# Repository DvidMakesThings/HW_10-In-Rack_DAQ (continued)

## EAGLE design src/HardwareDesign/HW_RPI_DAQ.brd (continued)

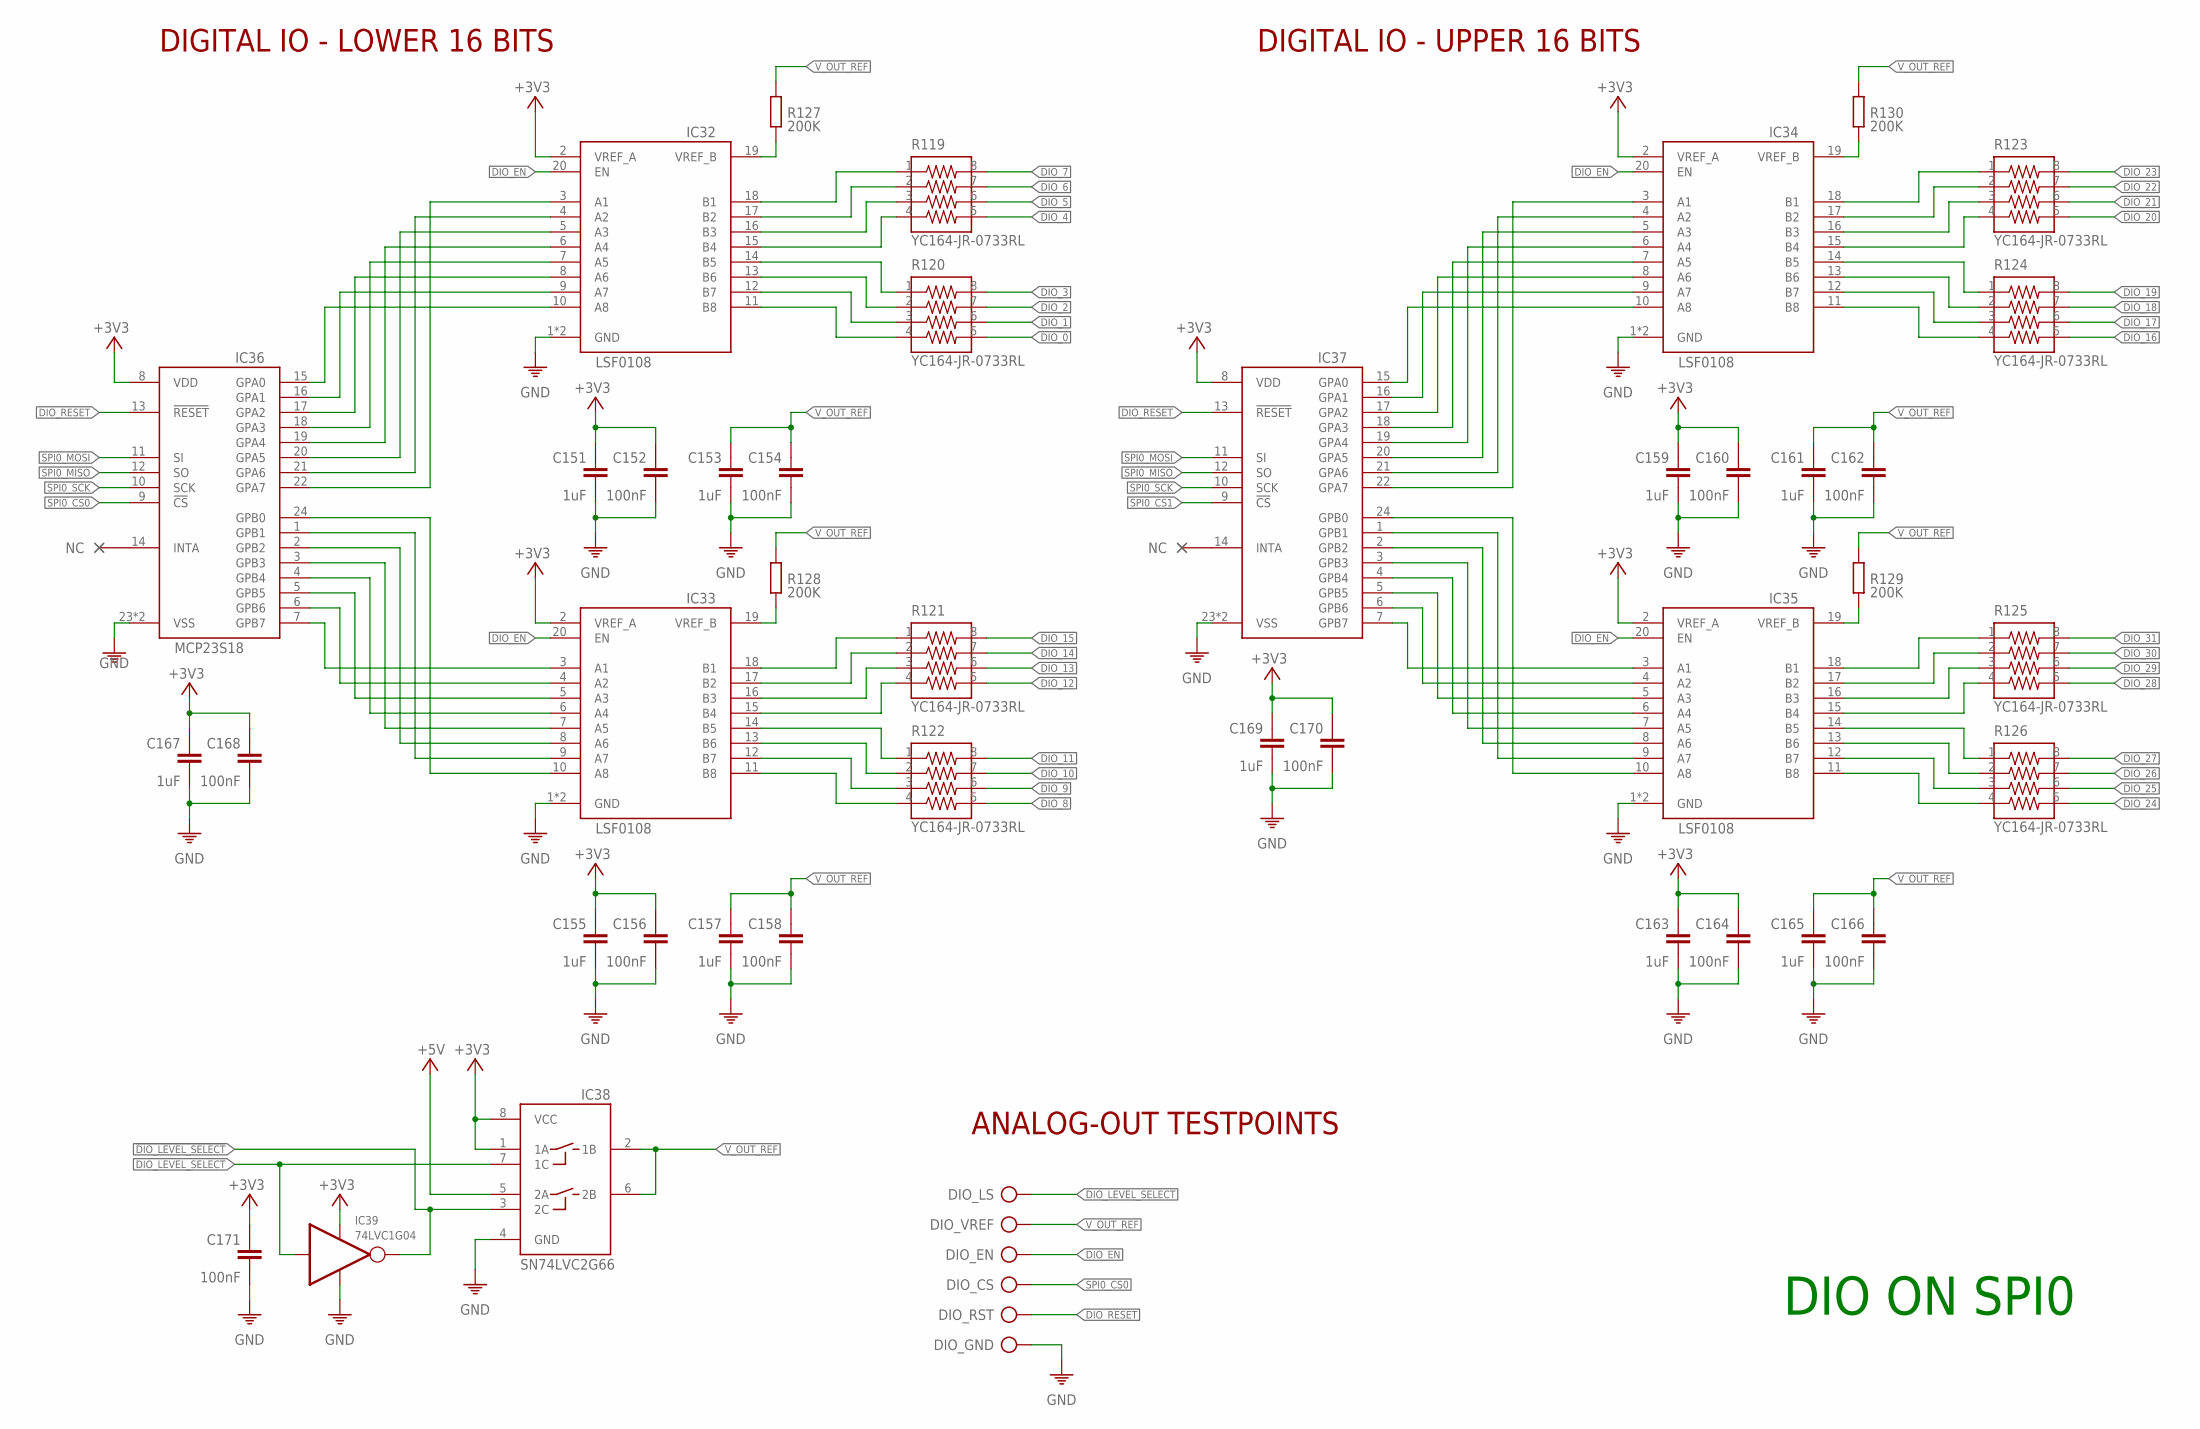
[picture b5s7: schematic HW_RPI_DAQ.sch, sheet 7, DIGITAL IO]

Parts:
C151, C153, C155, C157, C159, C161, C163, C165, C167, C169: 1uF; 0402
C152, C154, C156, C158, C160, C162, C164, C166, C168, C170: 100nF; 0402
C171: 100nF; 0603
DIO_CS: TP
DIO_EN: TP
DIO_GND: TP
DIO_LS: TP
DIO_RST: TP
DIO_VREF: TP
IC32, IC33, IC34, IC35: LSF0108; VQFN20
IC36, IC37: MCP23S18; QFN50P400X400X100-25T265
IC38: SN74LVC2G66; SOP50P310X90-8N
IC39: 74LVC1G04; SOT95P280X145-5N
R119, R120, R121, R122, R123, R124, R125, R126: YC164-JR-0733RL
R127, R128, R129, R130: 200K; 0402

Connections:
!DIO_LEVEL_SELECT: IC38.3 (2C), IC39.4 (OUT)
+3V3: C151.1, C152.1, C155.1, C156.1, C159.1, C160.1, C163.1, C164.1, C167.1, C168.1, C169.1, C170.1, C171.1, IC32.2 (VREF_A), IC33.2 (VREF_A), IC34.2 (VREF_A), IC35.2 (VREF_A), IC36.8 (VDD), IC37.8 (VDD), IC38.1 (1A), IC38.8 (VCC), IC39.5 (V+); also elsewhere on the board
+5V: IC38.5 (2A); also elsewhere on the board
DIO_0: R120.5; also elsewhere on the board
DIO_1: R120.6; also elsewhere on the board
DIO_2: R120.7; also elsewhere on the board
DIO_3: R120.8; also elsewhere on the board
DIO_4: R119.5; also elsewhere on the board
DIO_5: R119.6; also elsewhere on the board
DIO_6: R119.7; also elsewhere on the board
DIO_7: R119.8; also elsewhere on the board
DIO_8: R122.5; also elsewhere on the board
DIO_9: R122.6; also elsewhere on the board
DIO_10: R122.7; also elsewhere on the board
DIO_11: R122.8; also elsewhere on the board
DIO_12: R121.5; also elsewhere on the board
DIO_13: R121.6; also elsewhere on the board
DIO_14: R121.7; also elsewhere on the board
DIO_15: R121.8; also elsewhere on the board
DIO_16: R124.5; also elsewhere on the board
DIO_17: R124.6; also elsewhere on the board
DIO_18: R124.7; also elsewhere on the board
DIO_19: R124.8; also elsewhere on the board
DIO_20: R123.5; also elsewhere on the board
DIO_21: R123.6; also elsewhere on the board
DIO_22: R123.7; also elsewhere on the board
DIO_23: R123.8; also elsewhere on the board
DIO_24: R126.5; also elsewhere on the board
DIO_25: R126.6; also elsewhere on the board
DIO_26: R126.7; also elsewhere on the board
DIO_27: R126.8; also elsewhere on the board
DIO_28: R125.5; also elsewhere on the board
DIO_29: R125.6; also elsewhere on the board
DIO_30: R125.7; also elsewhere on the board
DIO_31: R125.8; also elsewhere on the board
DIO_EN: DIO_EN.TP, IC32.20 (EN), IC33.20 (EN), IC34.20 (EN), IC35.20 (EN); also elsewhere on the board
DIO_LEVEL_SELECT: DIO_LS.TP, IC38.7 (1C), IC39.2 (IN); also elsewhere on the board
DIO_RESET: DIO_RST.TP, IC36.13 (!RESET), IC37.13 (!RESET); also elsewhere on the board
GND: C151.2, C152.2, C153.2, C154.2, C155.2, C156.2, C157.2, C158.2, C159.2, C160.2, C161.2, C162.2, C163.2, C164.2, C165.2, C166.2, C167.2, C168.2, C169.2, C170.2, C171.2, DIO_GND.TP, IC32.1 (GND), IC32.PAD (GND), IC33.1 (GND), IC33.PAD (GND), IC34.1 (GND), IC34.PAD (GND), IC35.1 (GND), IC35.PAD (GND), IC36.23 (VSS), IC36.25 (VSS), IC37.23 (VSS), IC37.25 (VSS), IC38.4 (GND), IC39.3 (V-); also elsewhere on the board
unnamed: IC33.9 (A7), IC36.1 (GPB1)
unnamed: IC32.10 (A8), IC36.15 (GPA0)
unnamed: IC32.9 (A7), IC36.16 (GPA1)
unnamed: IC32.8 (A6), IC36.17 (GPA2)
unnamed: IC32.7 (A5), IC36.18 (GPA3)
unnamed: IC32.6 (A4), IC36.19 (GPA4)
unnamed: IC32.5 (A3), IC36.20 (GPA5)
unnamed: IC32.4 (A2), IC36.21 (GPA6)
unnamed: IC32.3 (A1), IC36.22 (GPA7)
unnamed: IC32.18 (B1), R119.1
unnamed: IC32.17 (B2), R119.2
unnamed: IC32.16 (B3), R119.3
unnamed: IC32.15 (B4), R119.4
unnamed: IC32.14 (B5), R120.1
unnamed: IC32.13 (B6), R120.2
unnamed: IC32.12 (B7), R120.3
unnamed: IC32.11 (B8), R120.4
unnamed: IC33.10 (A8), IC36.24 (GPB0)
unnamed: IC33.8 (A6), IC36.2 (GPB2)
unnamed: IC33.7 (A5), IC36.3 (GPB3)
unnamed: IC33.6 (A4), IC36.4 (GPB4)
unnamed: IC33.5 (A3), IC36.5 (GPB5)
unnamed: IC33.4 (A2), IC36.6 (GPB6)
unnamed: IC33.3 (A1), IC36.7 (GPB7)
unnamed: IC33.18 (B1), R121.1
unnamed: IC33.17 (B2), R121.2
unnamed: IC33.16 (B3), R121.3
unnamed: IC33.15 (B4), R121.4
unnamed: IC33.14 (B5), R122.1
unnamed: IC33.13 (B6), R122.2
unnamed: IC33.12 (B7), R122.3
unnamed: IC33.11 (B8), R122.4
unnamed: IC34.10 (A8), IC37.15 (GPA0)
unnamed: IC34.9 (A7), IC37.16 (GPA1)
unnamed: IC34.8 (A6), IC37.17 (GPA2)
unnamed: IC34.7 (A5), IC37.18 (GPA3)
unnamed: IC34.6 (A4), IC37.19 (GPA4)
unnamed: IC34.5 (A3), IC37.20 (GPA5)
unnamed: IC34.4 (A2), IC37.21 (GPA6)
unnamed: IC34.3 (A1), IC37.22 (GPA7)
unnamed: IC34.18 (B1), R123.1
unnamed: IC34.17 (B2), R123.2
unnamed: IC34.16 (B3), R123.3
unnamed: IC34.15 (B4), R123.4
unnamed: IC34.14 (B5), R124.1
unnamed: IC34.13 (B6), R124.2
unnamed: IC34.12 (B7), R124.3
unnamed: IC34.11 (B8), R124.4
unnamed: IC35.8 (A6), IC37.2 (GPB2)
unnamed: IC35.7 (A5), IC37.3 (GPB3)
unnamed: IC35.6 (A4), IC37.4 (GPB4)
unnamed: IC35.5 (A3), IC37.5 (GPB5)
unnamed: IC35.4 (A2), IC37.6 (GPB6)
unnamed: IC35.3 (A1), IC37.7 (GPB7)
unnamed: IC35.9 (A7), IC37.1 (GPB1)
unnamed: IC35.10 (A8), IC37.24 (GPB0)
unnamed: IC35.18 (B1), R125.1
unnamed: IC35.17 (B2), R125.2
unnamed: IC35.16 (B3), R125.3
unnamed: IC35.15 (B4), R125.4
unnamed: IC35.14 (B5), R126.1
unnamed: IC35.13 (B6), R126.2
unnamed: IC35.12 (B7), R126.3
unnamed: IC35.11 (B8), R126.4
unnamed: IC32.19 (VREF_B), R127.1
unnamed: IC33.19 (VREF_B), R128.1
unnamed: IC35.19 (VREF_B), R129.1
unnamed: IC34.19 (VREF_B), R130.1
SPI0_CS0: DIO_CS.TP, IC36.9 (!CS); also elsewhere on the board
SPI0_CS1: IC37.9 (!CS); also elsewhere on the board
SPI0_MISO: IC36.12 (SO), IC37.12 (SO); also elsewhere on the board
SPI0_MOSI: IC36.11 (SI), IC37.11 (SI); also elsewhere on the board
SPI0_SCK: IC36.10 (SCK), IC37.10 (SCK); also elsewhere on the board
V_OUT_REF: C153.1, C154.1, C157.1, C158.1, C161.1, C162.1, C165.1, C166.1, DIO_VREF.TP, IC38.2 (1B), IC38.6 (2B), R127.2, R128.2, R129.2, R130.2

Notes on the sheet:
DIGITAL IO - LOWER 16 BITS
DIGITAL IO - UPPER 16 BITS
ANALOG-OUT TESTPOINTS
DIO ON SPI0

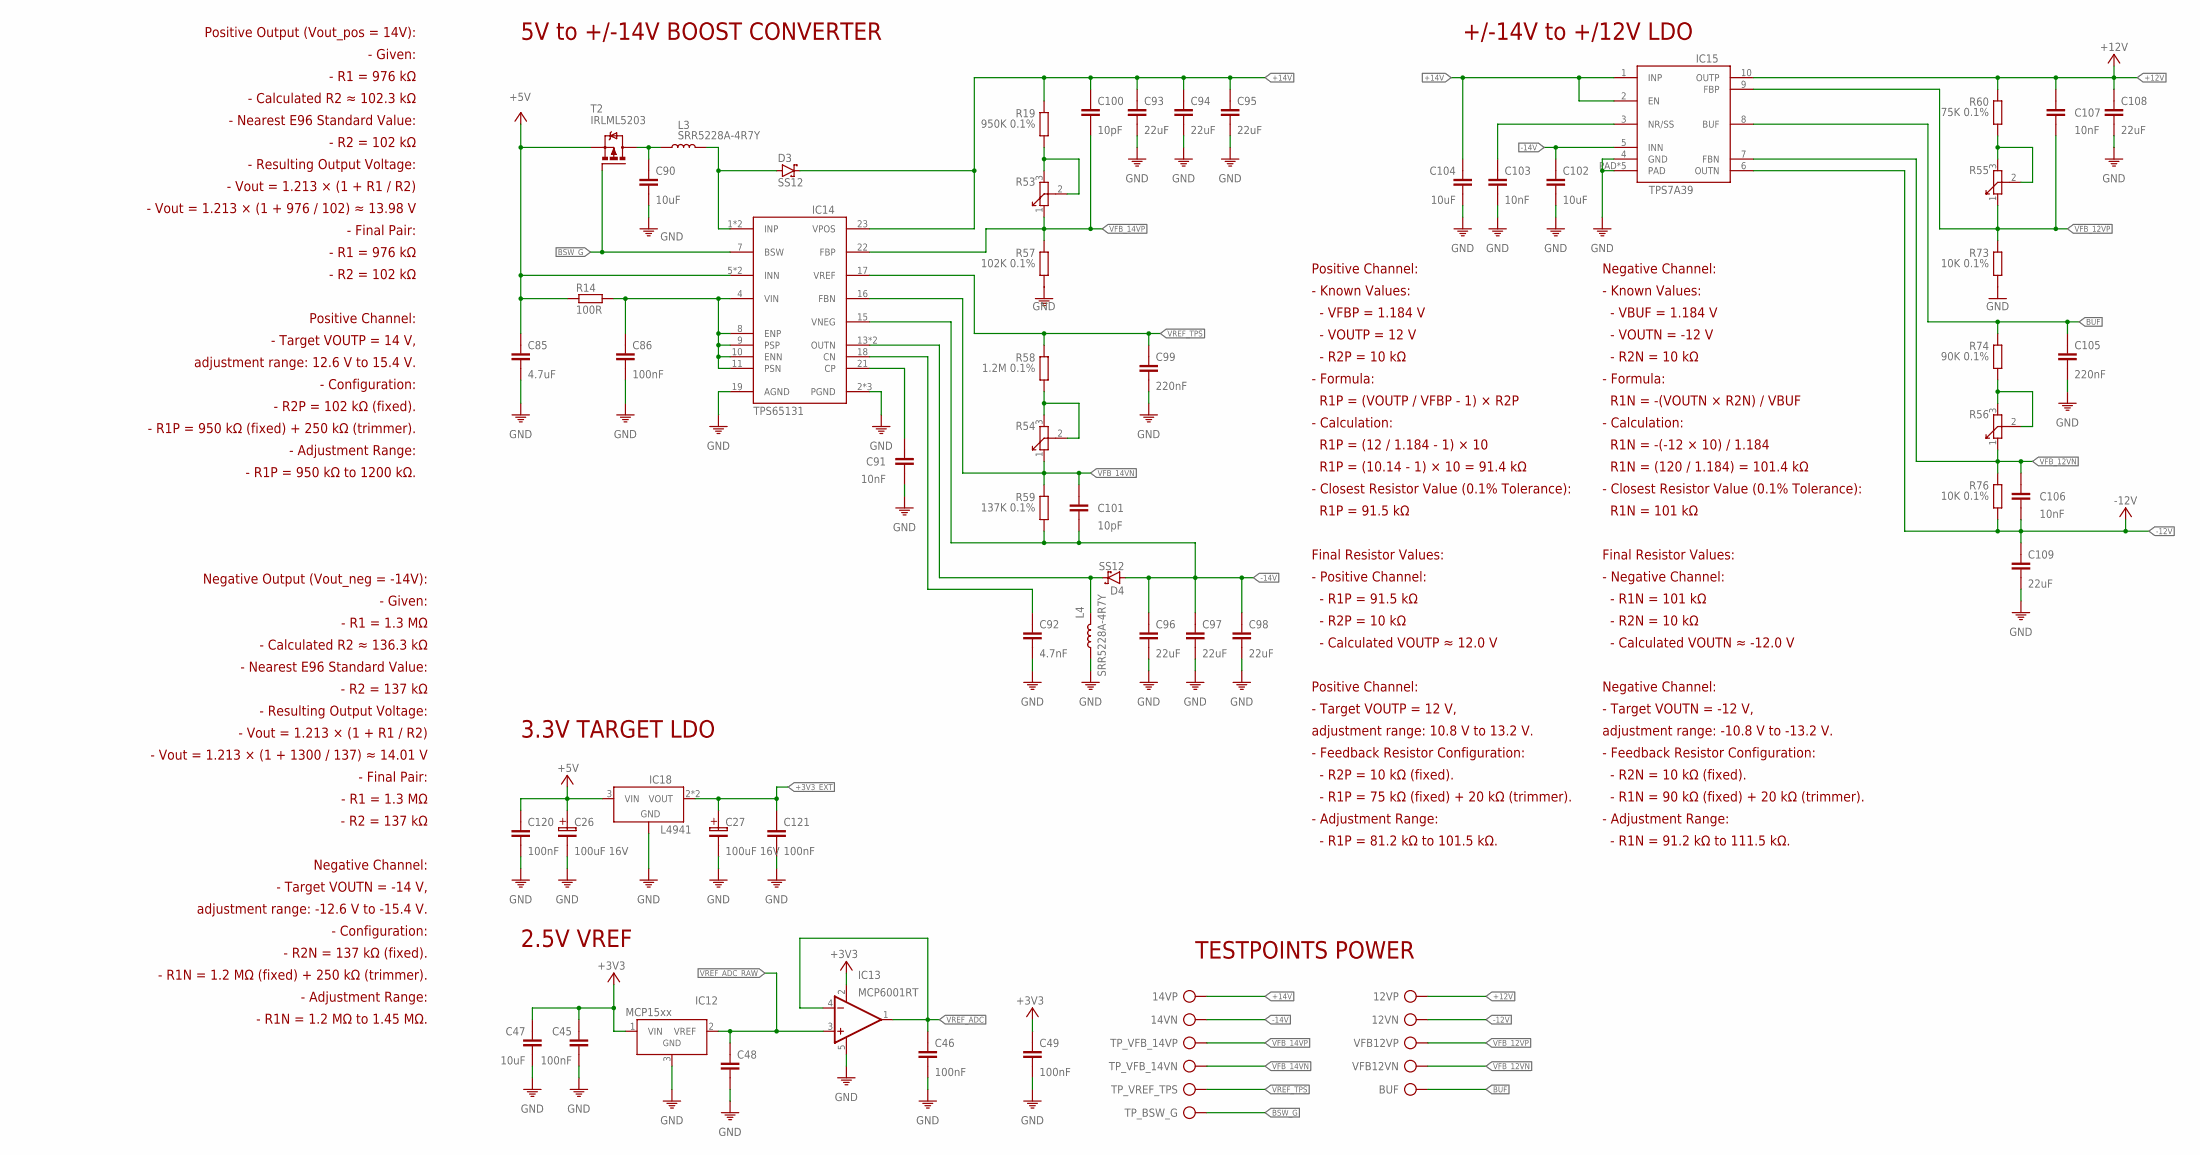
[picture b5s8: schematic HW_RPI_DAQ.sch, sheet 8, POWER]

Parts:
12VN, 12VP, 14VN, 14VP: TP
BUF: TP
C26, C27: 100uF 16V; 100UF-16V
C45, C46, C49, C120, C121: 100nF; 0402
C47, C90: 10uF; 0805
C48: C0805; 0805
C85: 4.7uF; 0805
C86: 100nF; 0805
C91: 10nF; 0805
C92: 4.7nF; 0805
C93, C94, C95, C96, C97, C98, C108, C109: 22uF; 1206
C99, C105: 220nF; 0402
C100, C101: 10pF; 0402
C102, C104: 10uF; 1206
C103, C106, C107: 10nF; 0402
D3, D4: SS12; SMA
IC12: MCP1525T-I/TT; SOT23
IC13: MCP6001RT; SOT23-5
IC14: TPS65131; VQFN24-4X4-THERMAL2.5X2.5
IC15: TPS7A39; WSON10-3X3
IC18: LDL1117S33R; SOT230
L3, L4: SRR5228A-4R7Y; SRR5228A
R14: 100R; 1206
R19: 950K 0.1%; 0402
R53, R54, R55, R56: R-TRIM; TC33X
R57: 102K 0.1%; 0402
R58: 1.2M 0.1%; 0402
R59: 137K 0.1%; 0402
R60: 75K 0.1%; 0402
R73, R76: 10K 0.1%; 0402
R74: 90K 0.1%; 0402
T2: IRLML5203; MICRO3
TP_BSW_G: TP
TP_VFB_14VN, TP_VFB_14VP: TP
TP_VREF_TPS: TP
VFB12VN, VFB12VP: TP

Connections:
+3V3: C45.1, C47.1, C49.1, IC12.1 (VIN), IC13.2 (V+); also elsewhere on the board
+3V3_EXT: C27.1, C121.1, IC18.2 (VOUT), IC18.4 (VOUT); also elsewhere on the board
+5V: C26.1, C85.1, C120.1, IC14.5 (INN), IC14.6 (INN), IC18.3 (VIN), R14.2, T2.2 (S); also elsewhere on the board
+12V: 12VP.TP, C107.2, C108.1, IC15.10 (OUTP), R60.1; also elsewhere on the board
+14V: 14VP.TP, C93.1, C94.1, C95.1, C100.1, C104.1, D3.C, IC14.23 (VPOS), IC15.1 (INP), IC15.2 (EN), R19.1
-12V: 12VN.TP, C106.1, C109.1, IC15.6 (OUTN), R76.2; also elsewhere on the board
-14V: 14VN.TP, C96.1, C97.1, C98.1, C101.1, C102.1, D4.A, IC14.15 (VNEG), IC15.5 (INN), R59.2
BSW_G: IC14.7 (BSW), T2.1 (G), TP_BSW_G.TP
BUF: BUF.TP, C105.2, IC15.8 (BUF), R74.1
GND: C26.2, C27.2, C45.2, C46.2, C47.2, C48.2, C49.2, C85.2, C86.2, C90.2, C91.2, C92.2, C93.2, C94.2, C95.2, C96.2, C97.2, C98.2, C99.1, C102.2, C103.2, C104.2, C105.1, C108.2, C109.2, C120.2, C121.2, IC12.3 (GND), IC13.5 (V-), IC14.2 (PGND), IC14.3 (PGND), IC14.19 (AGND), IC14.25 (PGND), IC15.4 (GND), IC15.PAD, IC15.PAD1 (PAD), IC15.PAD2 (PAD), IC15.PAD3 (PAD), IC15.PAD4 (PAD), IC18.1 (GND), L4.1, R57.2, R73.2; also elsewhere on the board
unnamed: D3.A, IC14.1 (INP), IC14.24 (INP), L3.2
unnamed: C90.1, L3.1, T2.3 (D)
unnamed: C86.1, IC14.4 (VIN), IC14.8 (ENP), IC14.9 (PSP), IC14.10 (ENN), IC14.11 (PSN), R14.1
unnamed: C91.1, IC14.21 (CP)
unnamed: C92.1, IC14.18 (CN)
unnamed: D4.C, IC14.13 (OUTN), IC14.14 (OUTN), L4.2
unnamed: R55.2, R55.3, R60.2
unnamed: C103.1, IC15.3 (NR/SS)
unnamed: R56.2, R56.3, R74.2
unnamed: R19.2, R53.2, R53.3
unnamed: R54.2, R54.3, R58.2
VFB_12VN: C106.2, IC15.7 (FBN), R56.1, R76.1, VFB12VN.TP
VFB_12VP: C107.1, IC15.9 (FBP), R55.1, R73.1, VFB12VP.TP
VFB_14VN: C101.2, IC14.16 (FBN), R54.1, R59.1, TP_VFB_14VN.TP
VFB_14VP: C100.2, IC14.22 (FBP), R53.1, R57.1, TP_VFB_14VP.TP
VREF_ADC: C46.1, IC13.1 (OUT), IC13.4 (-IN); also elsewhere on the board
VREF_ADC_RAW: C48.1, IC12.2 (VREF), IC13.3 (+IN); also elsewhere on the board
VREF_TPS: C99.2, IC14.17 (VREF), R58.1, TP_VREF_TPS.TP

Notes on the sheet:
3.3V TARGET LDO
2.5V VREF
5V to +/-14V BOOST CONVERTER
Positive Output (Vout_pos = 14V): - Given: - R1 = 976 kΩ - Calculated R2 ≈ 102.3 kΩ - Nearest E96 Standard Value: - R2 = 102 kΩ - Resulting Output Voltage: - Vout = 1.213 × (1 + R1 / R2) - Vout = 1.213 × (1 + 976 / 102) ≈ 13.98 V - Final Pair: - R1 = 976 kΩ - R2 = 102 kΩ Positive Channel: - Target 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
Negative Output (Vout_neg = -14V): - Given: - R1 = 1.3 MΩ - Calculated R2 ≈ 136.3 kΩ - Nearest E96 Standard Value: - R2 = 137 kΩ - Resulting Output Voltage: - Vout = 1.213 × (1 + R1 / R2) - Vout = 1.213 × (1 + 1300 / 137) ≈ 14.01 V - Final Pair: - R1 = 1.3 MΩ - R2 = 137 kΩ Negative Channel: - Targe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
Positive Channel: - Known Values: - VFBP = 1.184 V - VOUTP = 12 V - R2P = 10 kΩ - Formula: R1P = (VOUTP / VFBP - 1) × R2P - Calculation: R1P = (12 / 1.184 - 1) × 10 R1P = (10.14 - 1) × 10 = 91.4 kΩ - Closest Resistor Value (0.1% Tolerance): R1P = 91.5 kΩ Final Resistor Values: - Positive Channel: -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
Negative Channel: - Known Values: - VBUF = 1.184 V - VOUTN = -12 V - R2N = 10 kΩ - Formula: R1N = -(VOUTN × R2N) / VBUF - Calculation: R1N = -(-12 × 10) / 1.184 R1N = (120 / 1.184) = 101.4 kΩ - Closest Resistor Value (0.1% Tolerance): R1N = 101 kΩ Final Resistor Values: - Negative Channel: - R1N = 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
+/-14V to +/12V LDO
TESTPOINTS POWER

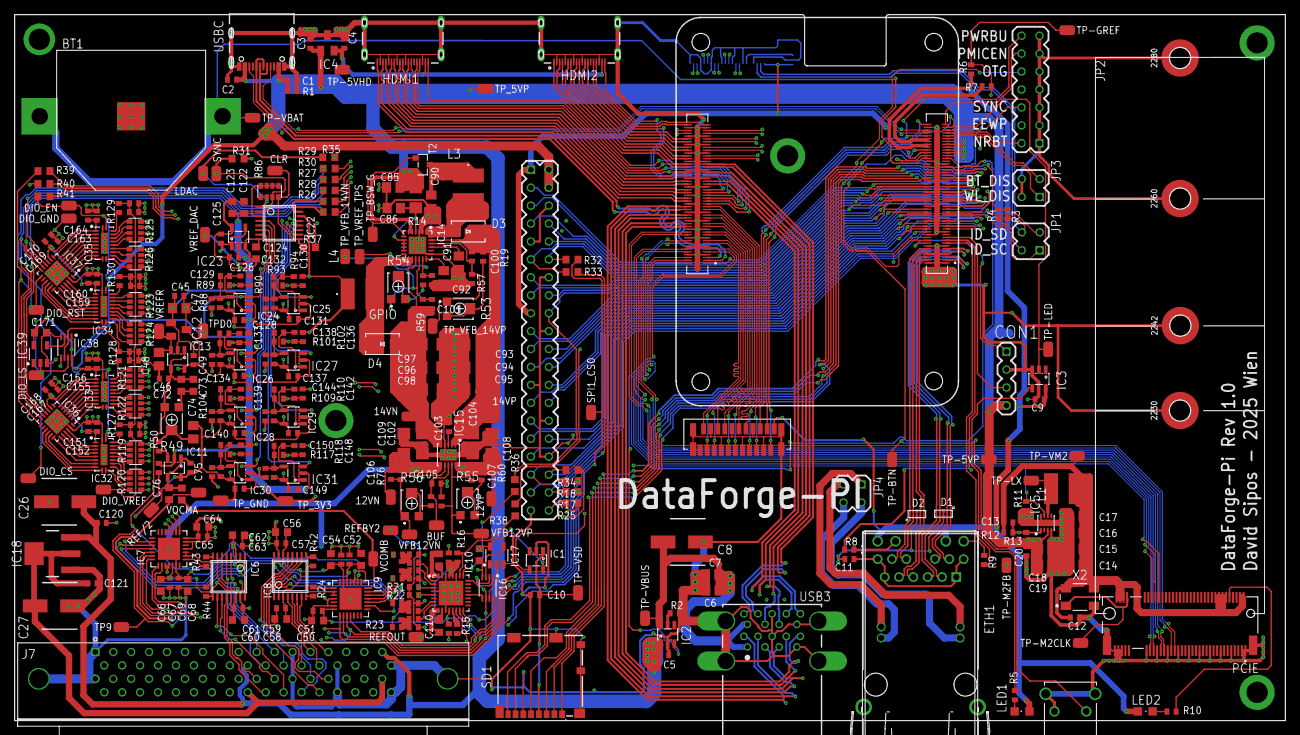
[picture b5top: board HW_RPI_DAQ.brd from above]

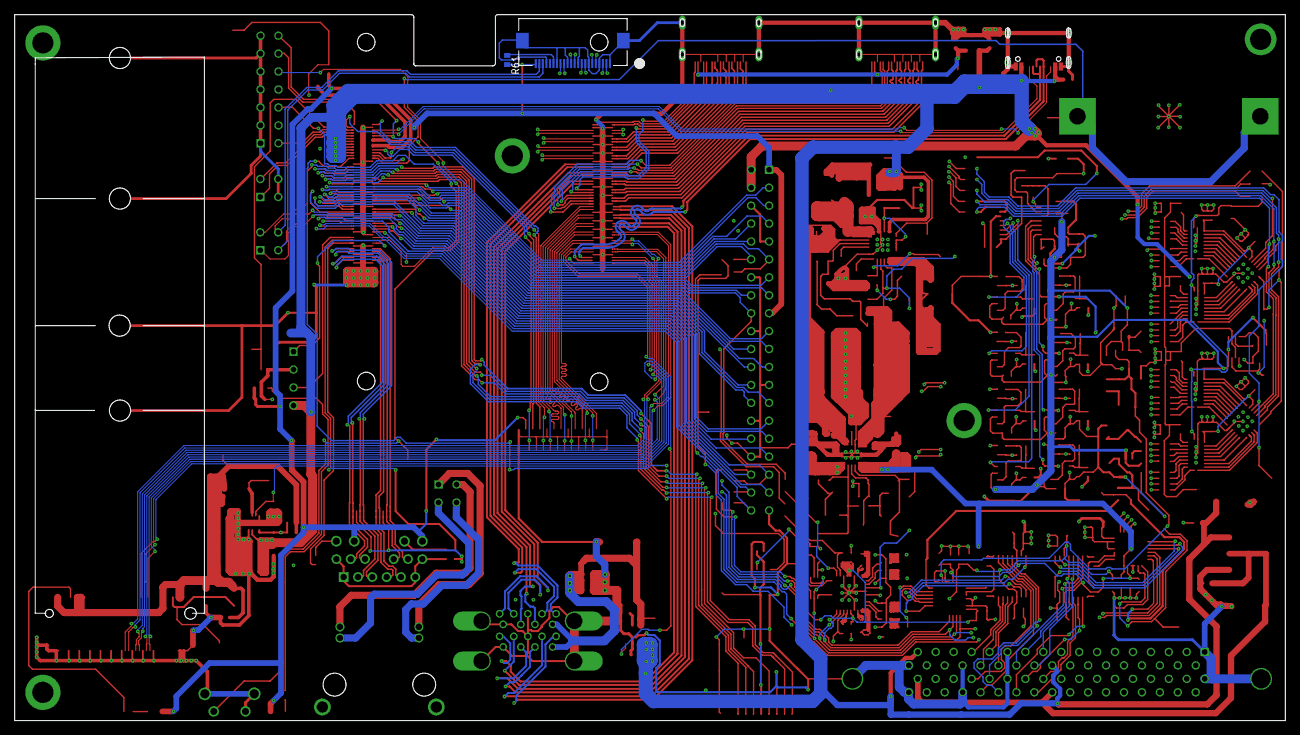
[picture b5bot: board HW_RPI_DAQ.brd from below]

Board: 4 copper layers, 180.0 x 100.0 mm, 364 parts (2 on the bottom side), 398 nets.

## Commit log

2025-01-19 initial creation
2025-01-21 schematic-baseline finished
2025-01-21 add pdf schematics
2025-01-22 add DAQ to design
2025-01-23 add datasheets
2025-01-24 create PCB
2025-01-24 3D render
2025-01-25 update schematics with new testpoints
2025-01-25 update PDF schematics
2025-02-05 add documentation
2025-02-07 AIO Board ready
2025-02-08 finish DIO card desing
2025-02-08 Baseboard design ready
2025-02-09 finish PCB desing
2025-02-10 add diffpaircheck
2025-03-02 Redesign to reduce height
